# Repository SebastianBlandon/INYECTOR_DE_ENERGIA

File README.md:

# INYECTOR DE ENERGIA PARA EQUIPOS DE FIBRA OPTICA
Este repositorio contiene diseño de esquematico y placa desarrollado en EAGLE. EL fin del diseño es llevar energia desde postes de energia a los equipos de fibra optica de un empresa de telecomunicaciones que le proveea sus clientes energia para sus equipos de fibra (ONU - Optical Network Unit)

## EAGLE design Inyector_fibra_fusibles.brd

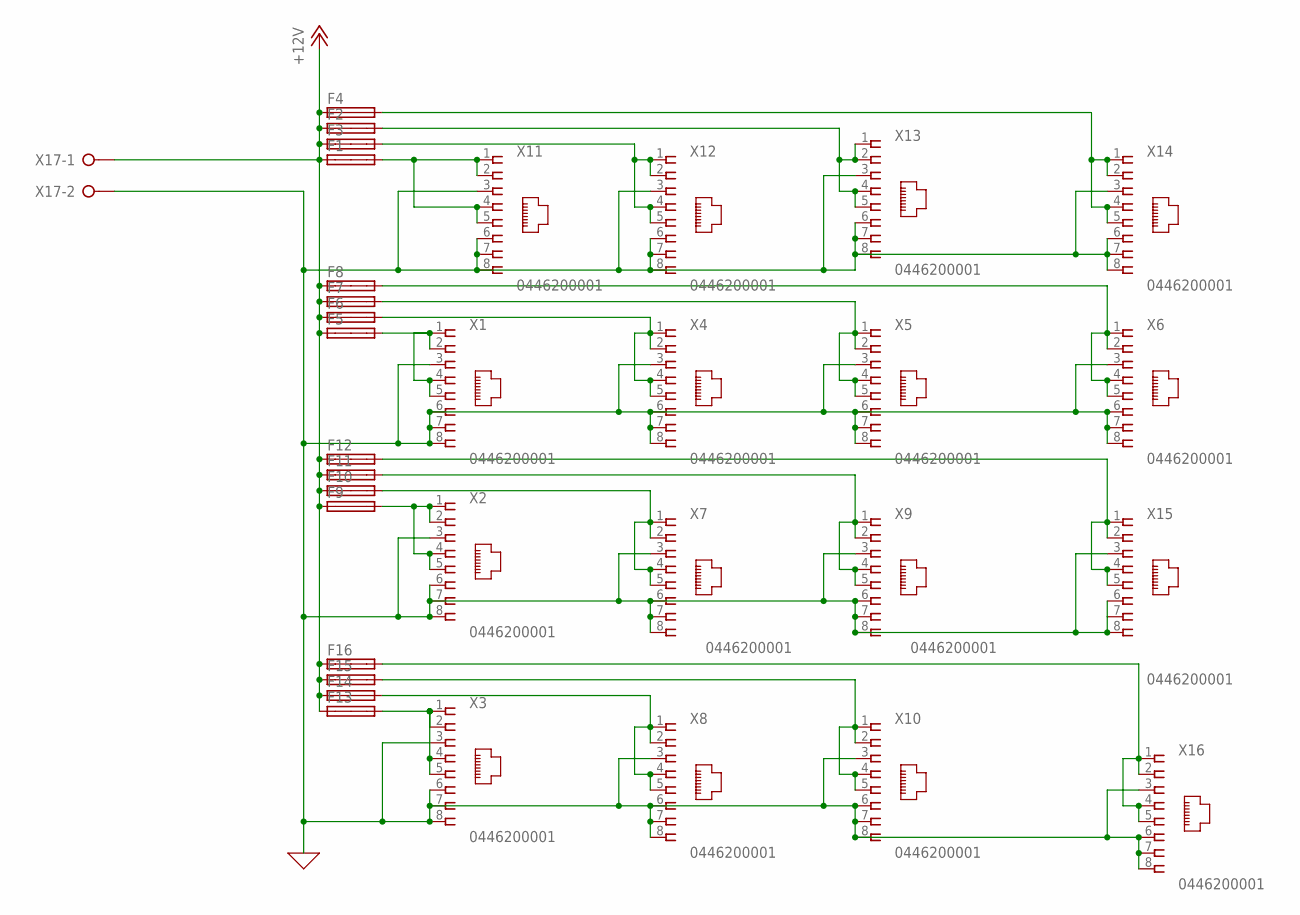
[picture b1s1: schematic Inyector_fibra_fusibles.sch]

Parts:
F1, F2, F3, F4, F5, F6, F7, F8, F9, F10, F11, F12, F13, F14, F15, F16: SHK20Q
X1, X2, X3, X4, X5, X6, X7, X8, X9, X10, X11, X12, X13, X14, X15, X16: 0446200001
X17: W237-02P; W237-132

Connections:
0: X1.3, X1.6, X1.7, X1.8, X2.3, X2.6, X2.7, X2.8, X3.3, X3.6, X3.7, X3.8, X4.3, X4.6, X4.7, X4.8, X5.3, X5.6, X5.7, X5.8, X6.3, X6.6, X6.7, X6.8, X7.3, X7.6, X7.7, X7.8, X8.3, X8.6, X8.7, X8.8, X9.3, X9.6, X9.7, X9.8, X10.3, X10.6, X10.7, X10.8, X11.3, X11.6, X11.7, X11.8, X12.3, X12.6, X12.7, X12.8, X13.3, X13.6, X13.7, X13.8, X14.3, X14.6, X14.7, X14.8, X15.3, X15.6, X15.7, X15.8, X16.3, X16.6, X16.7, X16.8, X17.2
+12V: F1.1A, F2.1A, F3.1A, F4.1A, F5.1A, F6.1A, F7.1A, F8.1A, F9.1A, F10.1A, F11.1A, F12.1A, F13.1A, F14.1A, F15.1A, F16.1A, X17.1
unnamed: F12.2A, X15.1, X15.2, X15.4, X15.5
unnamed: F6.2A, X4.1, X4.2, X4.4, X4.5
unnamed: F7.2A, X5.1, X5.2, X5.4, X5.5
unnamed: F1.2A, X11.1, X11.2, X11.4, X11.5
unnamed: F8.2A, X6.1, X6.2, X6.4, X6.5
unnamed: F3.2A, X12.1, X12.2, X12.4, X12.5
unnamed: F2.2A, X13.1, X13.2, X13.4, X13.5
unnamed: F4.2A, X14.1, X14.2, X14.4, X14.5
unnamed: F9.2A, X2.1, X2.2, X2.4, X2.5
unnamed: F5.2A, X1.1, X1.2, X1.4, X1.5
unnamed: F10.2A, X7.1, X7.2, X7.4, X7.5
unnamed: F11.2A, X9.1, X9.2, X9.4, X9.5
unnamed: F13.2A, X3.1, X3.2, X3.4, X3.5
unnamed: F16.2A, X16.1, X16.2, X16.4, X16.5
unnamed: F14.2A, X8.1, X8.2, X8.4, X8.5
unnamed: F15.2A, X10.1, X10.2, X10.4, X10.5

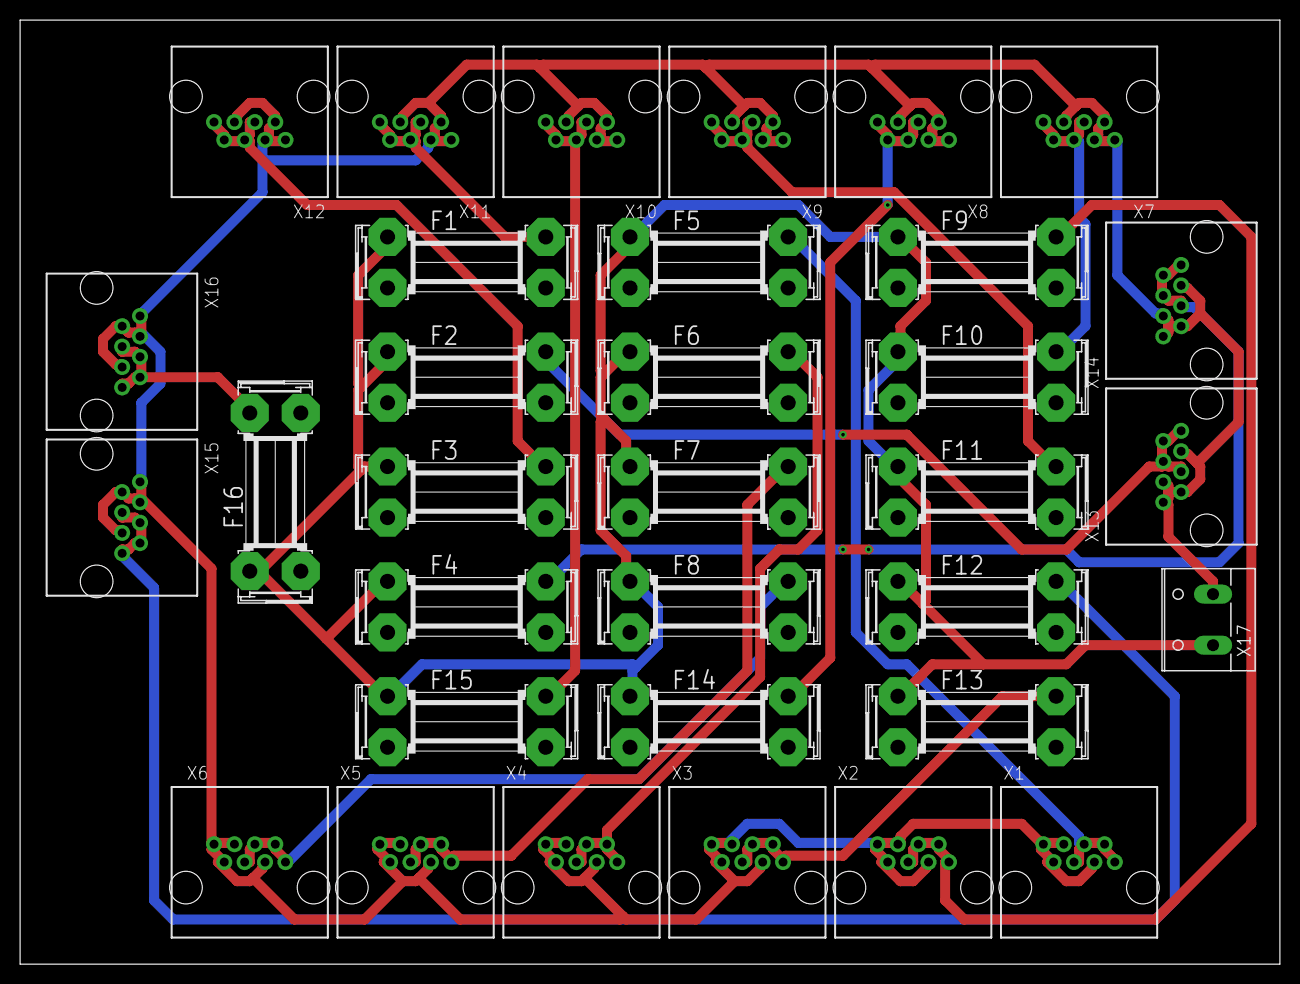
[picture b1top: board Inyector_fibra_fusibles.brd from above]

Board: 2 copper layers, 125.4 x 94.0 mm, 33 parts (0 on the bottom side), 18 nets.

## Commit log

2022-05-03 [ADDED] all files and folder
